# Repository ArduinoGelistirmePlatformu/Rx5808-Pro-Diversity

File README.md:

# Rx5808-Pro-Diversity
https://github.com/sheaivey/rx5808-pro-diversity

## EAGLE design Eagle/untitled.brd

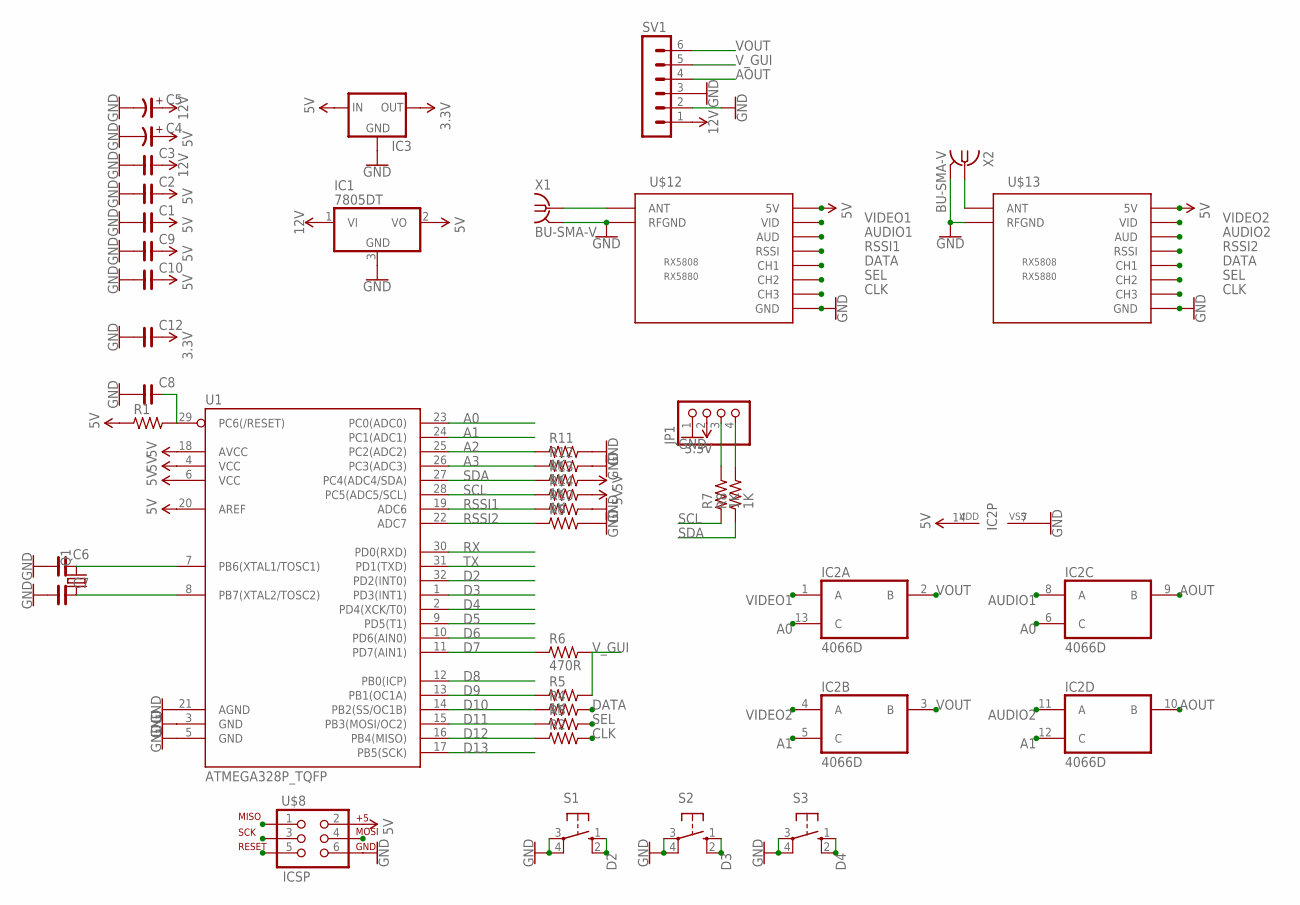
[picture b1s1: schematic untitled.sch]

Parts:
C1, C2, C3, C6, C7, C8, C9, C10, C12: C_0805; C0805
C4, C5: CP_6032-28; C6032-28/T
IC1: 7805DT; TO252
IC2: 4066D; SO14
IC3: LM1117; SOT223
JP1: PINHD-1X04_2.54-S; 1X04-S
Q1: CRYSTALHC49S; HC49/S
R1, R2, R3, R4, R9, R10: R_0805; R0805
R5, R7, R8, R11, R12, R13, R14: 1K; R0805
R6: 470R; R0805
S1, S2, S3: 10-XX; B3F-10XX
SV1: MA06-1
U1: ATMEGA328P_TQFP; TQFP32-08
U$8: ICSP; 2X3-NS
U$12, U$13: RX5808
X1, X2: BU-SMA-V

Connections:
3.3V: C12.2, IC3.2 (OUT), JP1.2
5V: C1.2, C2.2, C4.+, C9.2, C10.2, IC1.2 (VO), IC2.14 (VDD), IC3.3 (IN), R1.1, R13.2, R14.2, U1.4 (VCC), U1.6 (VCC), U1.18 (AVCC), U1.20 (AREF), U$8.2, U$12.VCC (5V), U$13.VCC (5V)
12V: C3.2, C5.+, IC1.1 (VI), SV1.1
A0: IC2.6 (C), IC2.13 (C), U1.23 (PC0(ADC0))
A1: IC2.5 (C), IC2.12 (C), U1.24 (PC1(ADC1))
A2: R11.1, U1.25 (PC2(ADC2))
A3: R12.1, U1.26 (PC3(ADC3))
AOUT: IC2.9 (B), IC2.10 (B), SV1.4
AUDIO1: IC2.8 (A), U$12.AUD
AUDIO2: IC2.11 (A), U$13.AUD
CLK: R2.2, U$12.CH3, U$13.CH3
D2: S1.1 (S), S1.2 (S1), U1.32 (PD2(INT0))
D3: S2.1 (S), S2.2 (S1), U1.1 (PD3(INT1))
D4: S3.1 (S), S3.2 (S1), U1.2 (PD4(XCK/T0))
D5: U1.9 (PD5(T1))
D6: U1.10 (PD6(AIN0))
D7: R6.1, U1.11 (PD7(AIN1))
D8: U1.12 (PB0(ICP))
D9: R5.1, U1.13 (PB1(OC1A))
D10: R4.1, U1.14 (PB2(SS/OC1B))
D11: R3.1, U1.15 (PB3(MOSI/OC2)), U$8.4
D12: R2.1, U1.16 (PB4(MISO)), U$8.1
D13: U1.17 (PB5(SCK)), U$8.3
DATA: R4.2, U$12.CH1, U$13.CH1
GND: C1.1, C2.1, C3.1, C4.-, C5.-, C6.1, C7.1, C8.1, C9.1, C10.1, C12.1, IC1.3 (GND), IC2.7 (VSS), IC3.1 (GND), JP1.1, R9.2, R10.2, R11.2, R12.2, S1.3, S1.4 (P1), S2.3, S2.4 (P1), S3.3, S3.4 (P1), SV1.2, SV1.3, U1.3 (GND), U1.5 (GND), U1.21 (AGND), U$8.6, U$12.GND@1 (GND), U$12.GND@2 (GND), U$12.RFGND@1 (RFGND), U$12.RFGND@2 (RFGND), U$13.GND@1 (GND), U$13.GND@2 (GND), U$13.RFGND@1 (RFGND), U$13.RFGND@2 (RFGND), X1.2, X1.3 (2), X1.4 (2), X1.5 (2), X2.2, X2.3 (2), X2.4 (2), X2.5 (2)
unnamed: JP1.3, R7.2
unnamed: C6.2, Q1.2, U1.7 (PB6(XTAL1/TOSC1))
unnamed: C7.2, Q1.1, U1.8 (PB7(XTAL2/TOSC2))
unnamed: JP1.4, R8.2
unnamed: U$12.ANT, X1.1
unnamed: U$13.ANT, X2.1
RSSI1: R10.1, U1.19 (ADC6), U$12.RSSI
RSSI2: R9.1, U1.22 (ADC7), U$13.RSSI
RST: C8.2, R1.2, U1.29 (PC6(/RESET)), U$8.5
RX: U1.30 (PD0(RXD))
SCL: R7.1, R14.1, U1.28 (PC5(ADC5/SCL))
SDA: R8.1, R13.1, U1.27 (PC4(ADC4/SDA))
SEL: R3.2, U$12.CH2, U$13.CH2
TX: U1.31 (PD1(TXD))
VIDEO1: IC2.1 (A), U$12.VID
VIDEO2: IC2.4 (A), U$13.VID
VOUT: IC2.2 (B), IC2.3 (B), SV1.6
V_GUI: R5.2, R6.2, SV1.5

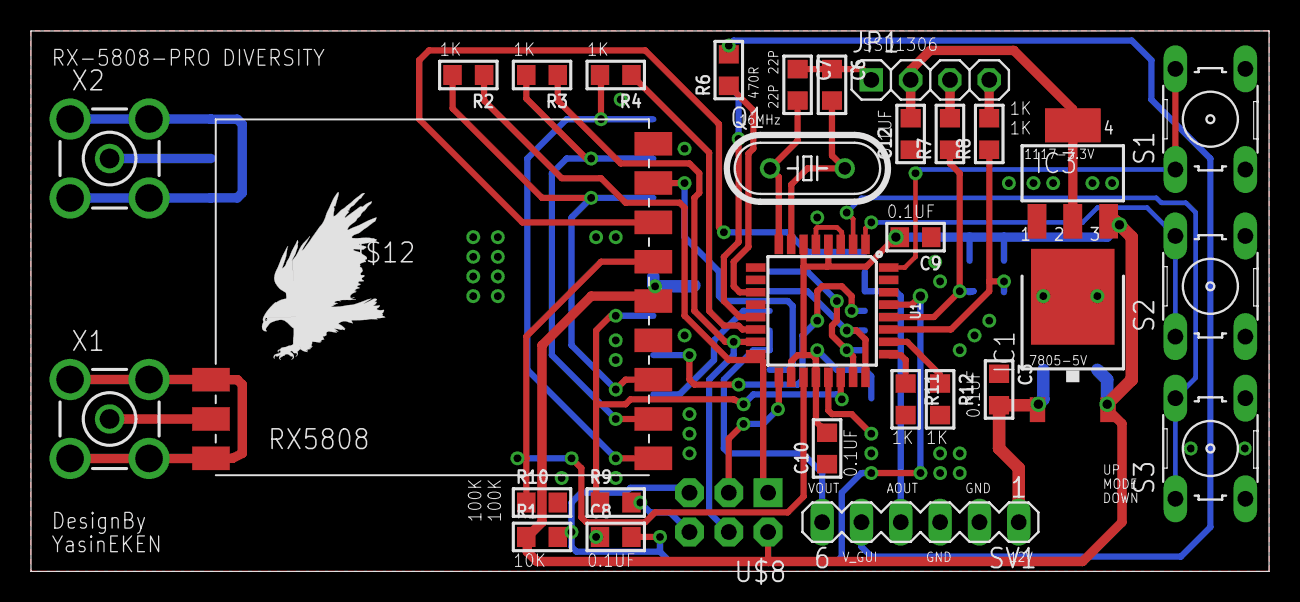
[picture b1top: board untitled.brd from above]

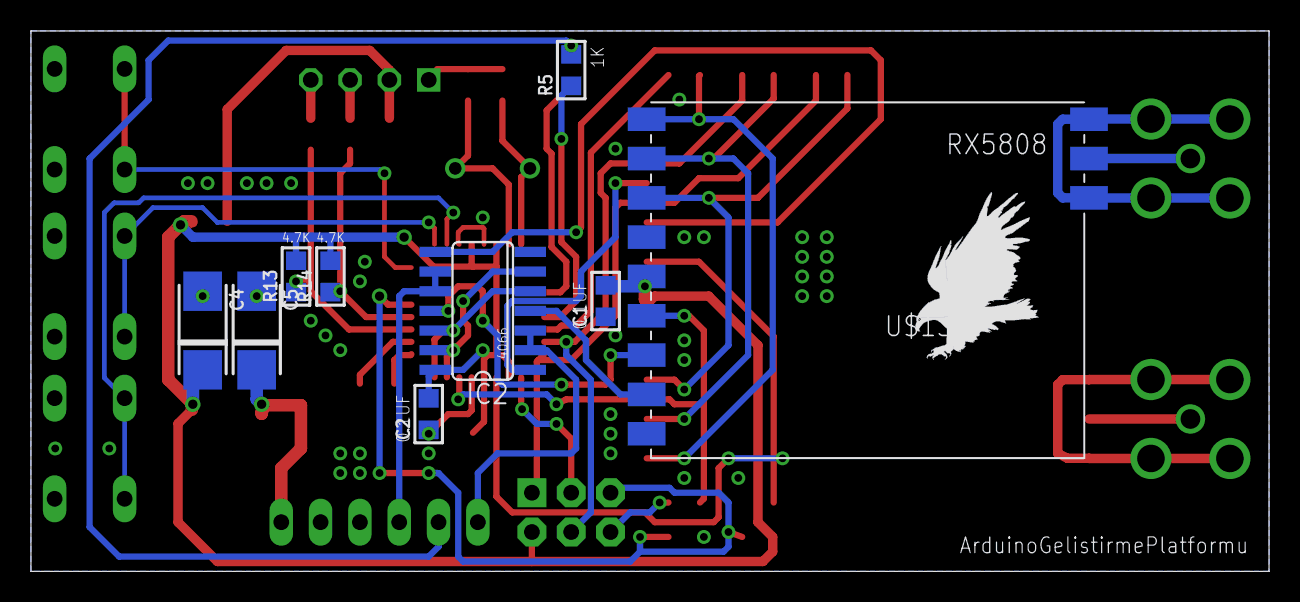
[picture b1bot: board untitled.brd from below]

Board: 2 copper layers, 80.0 x 34.9 mm, 43 parts (10 on the bottom side), 38 nets.

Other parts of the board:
U$10: LOGO
U$19, U$20: EAGLE-PLC-8MM

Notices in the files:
parts and their libraries:
Acap_BNM: Copyright (C) 2007, Bob Starr
SparkFun-IC-Microcontroller: Licensing: Creative Commons ShareAlike 4.0 International - https://creativecommons.org/licenses/by-sa/4.0
